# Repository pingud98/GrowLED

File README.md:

# GrowLED
PCB for red and blue LEDs

I had some spare Bivar SMP4-SBC-RB PLCC4 footprint LED's lying around so decided to make a board to use them in my hydroponics system.

All files are eagle cad. I've also panelised them to a 10x10cm board with 7 strips.

Licensed under the CERN OHL V1.2

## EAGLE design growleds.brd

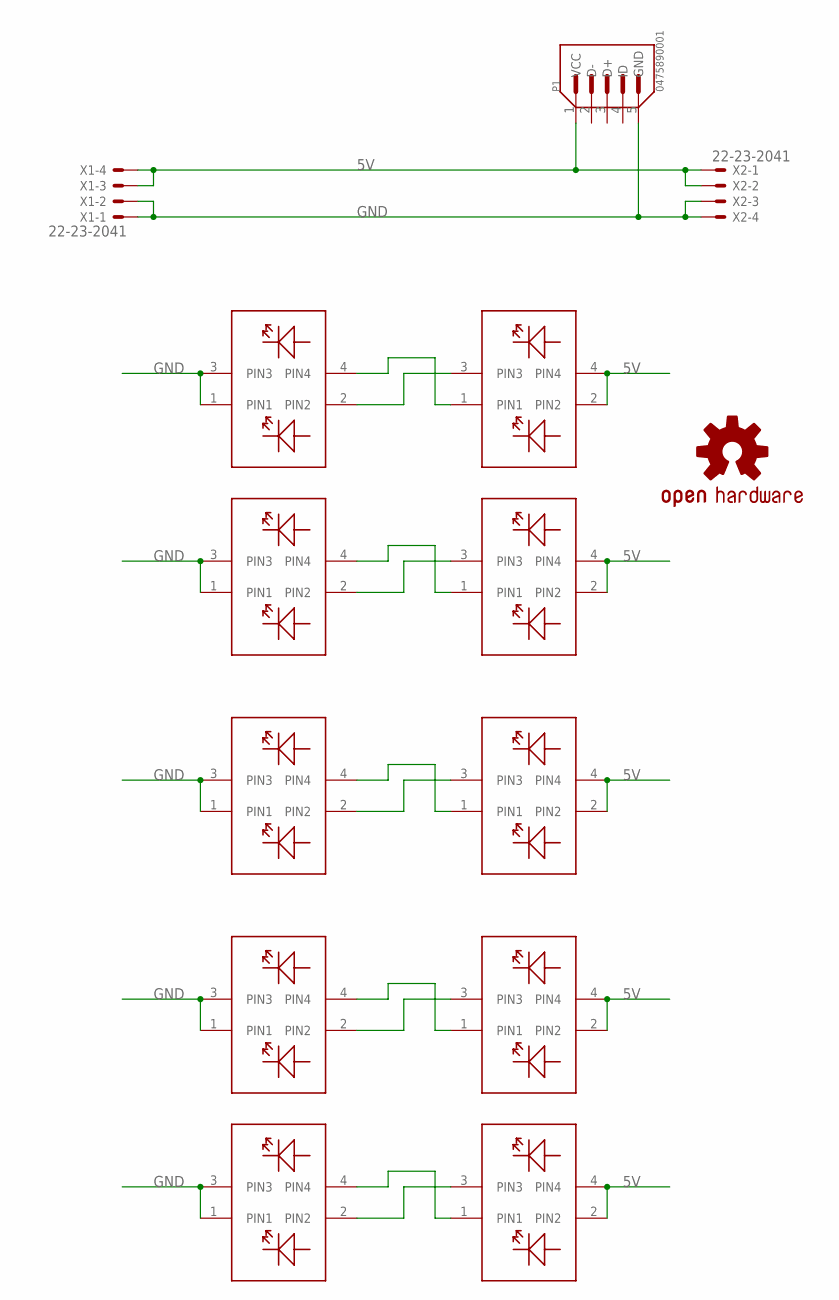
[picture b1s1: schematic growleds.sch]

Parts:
LOGO1: OSHW-LOGOM-COPPER; OSHW-LOGO-M_COPPER
P1: 0475890001; MOLEX_0475890001
U$1, U$2, U$3, U$4, U$5, U$6, U$7, U$8, U$9, U$10: RBLED; 4-PLCC
X1, X2: 22-23-2041

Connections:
5V: P1.1 (VCC), U$2.2 (PIN2), U$2.4 (PIN4), U$4.2 (PIN2), U$4.4 (PIN4), U$6.2 (PIN2), U$6.4 (PIN4), U$8.2 (PIN2), U$8.4 (PIN4), U$10.2 (PIN2), U$10.4 (PIN4), X1.3, X1.4, X2.1, X2.2
GND: P1.5 (GND), U$1.1 (PIN1), U$1.3 (PIN3), U$3.1 (PIN1), U$3.3 (PIN3), U$5.1 (PIN1), U$5.3 (PIN3), U$7.1 (PIN1), U$7.3 (PIN3), U$9.1 (PIN1), U$9.3 (PIN3), X1.1, X1.2, X2.3, X2.4
unnamed: U$1.2 (PIN2), U$2.3 (PIN3)
unnamed: U$1.4 (PIN4), U$2.1 (PIN1)
unnamed: U$3.2 (PIN2), U$4.3 (PIN3)
unnamed: U$3.4 (PIN4), U$4.1 (PIN1)
unnamed: U$5.2 (PIN2), U$6.3 (PIN3)
unnamed: U$5.4 (PIN4), U$6.1 (PIN1)
unnamed: U$7.2 (PIN2), U$8.3 (PIN3)
unnamed: U$7.4 (PIN4), U$8.1 (PIN1)
unnamed: U$9.2 (PIN2), U$10.3 (PIN3)
unnamed: U$9.4 (PIN4), U$10.1 (PIN1)

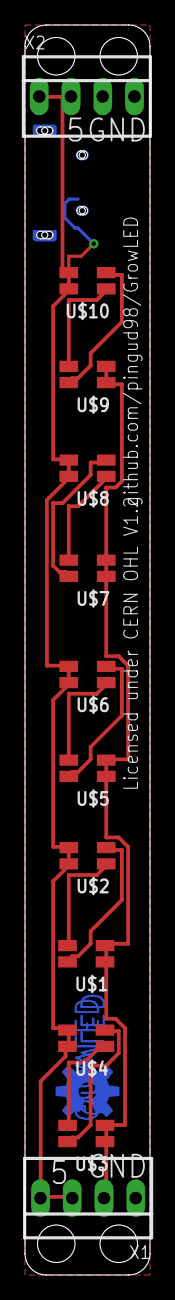
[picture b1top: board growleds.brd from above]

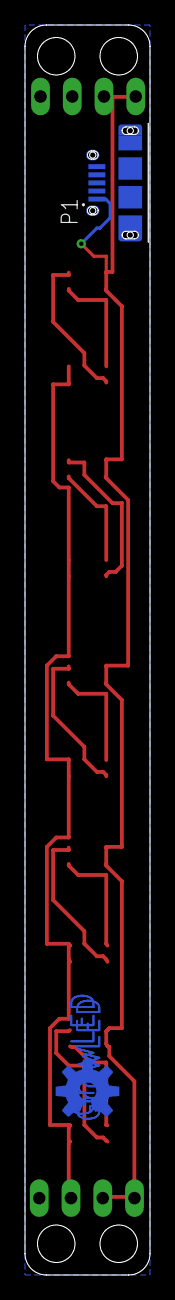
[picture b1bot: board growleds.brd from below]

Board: 2 copper layers, 10.0 x 100.0 mm, 14 parts (2 on the bottom side), 12 nets.

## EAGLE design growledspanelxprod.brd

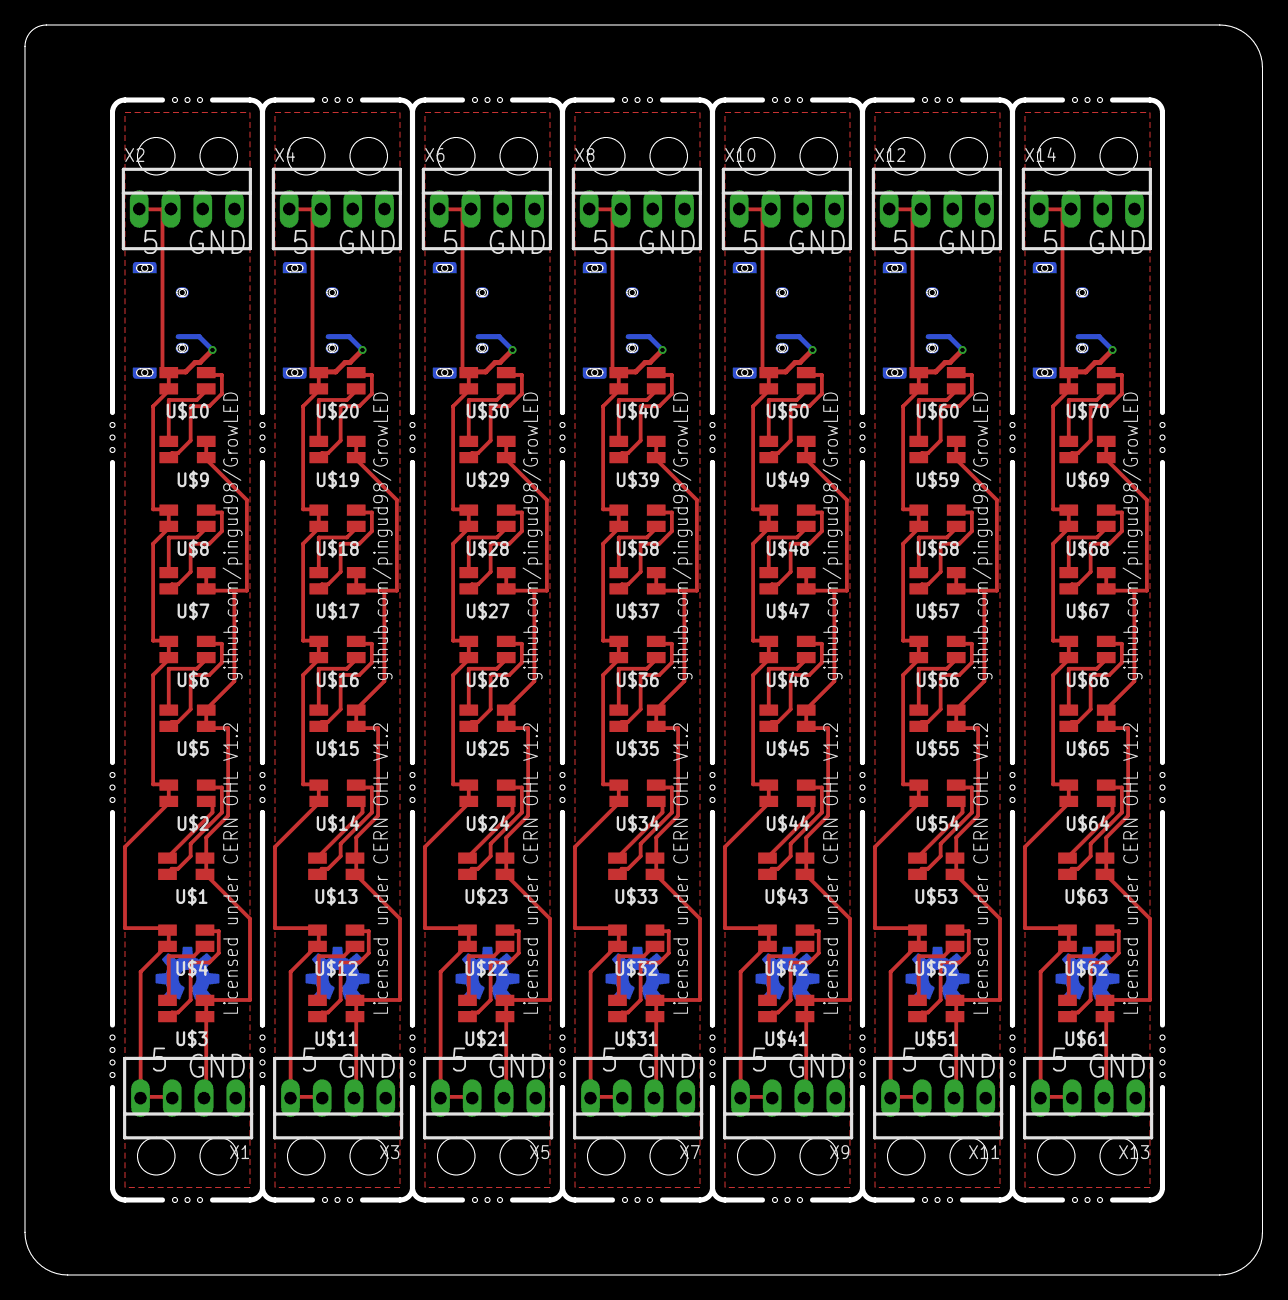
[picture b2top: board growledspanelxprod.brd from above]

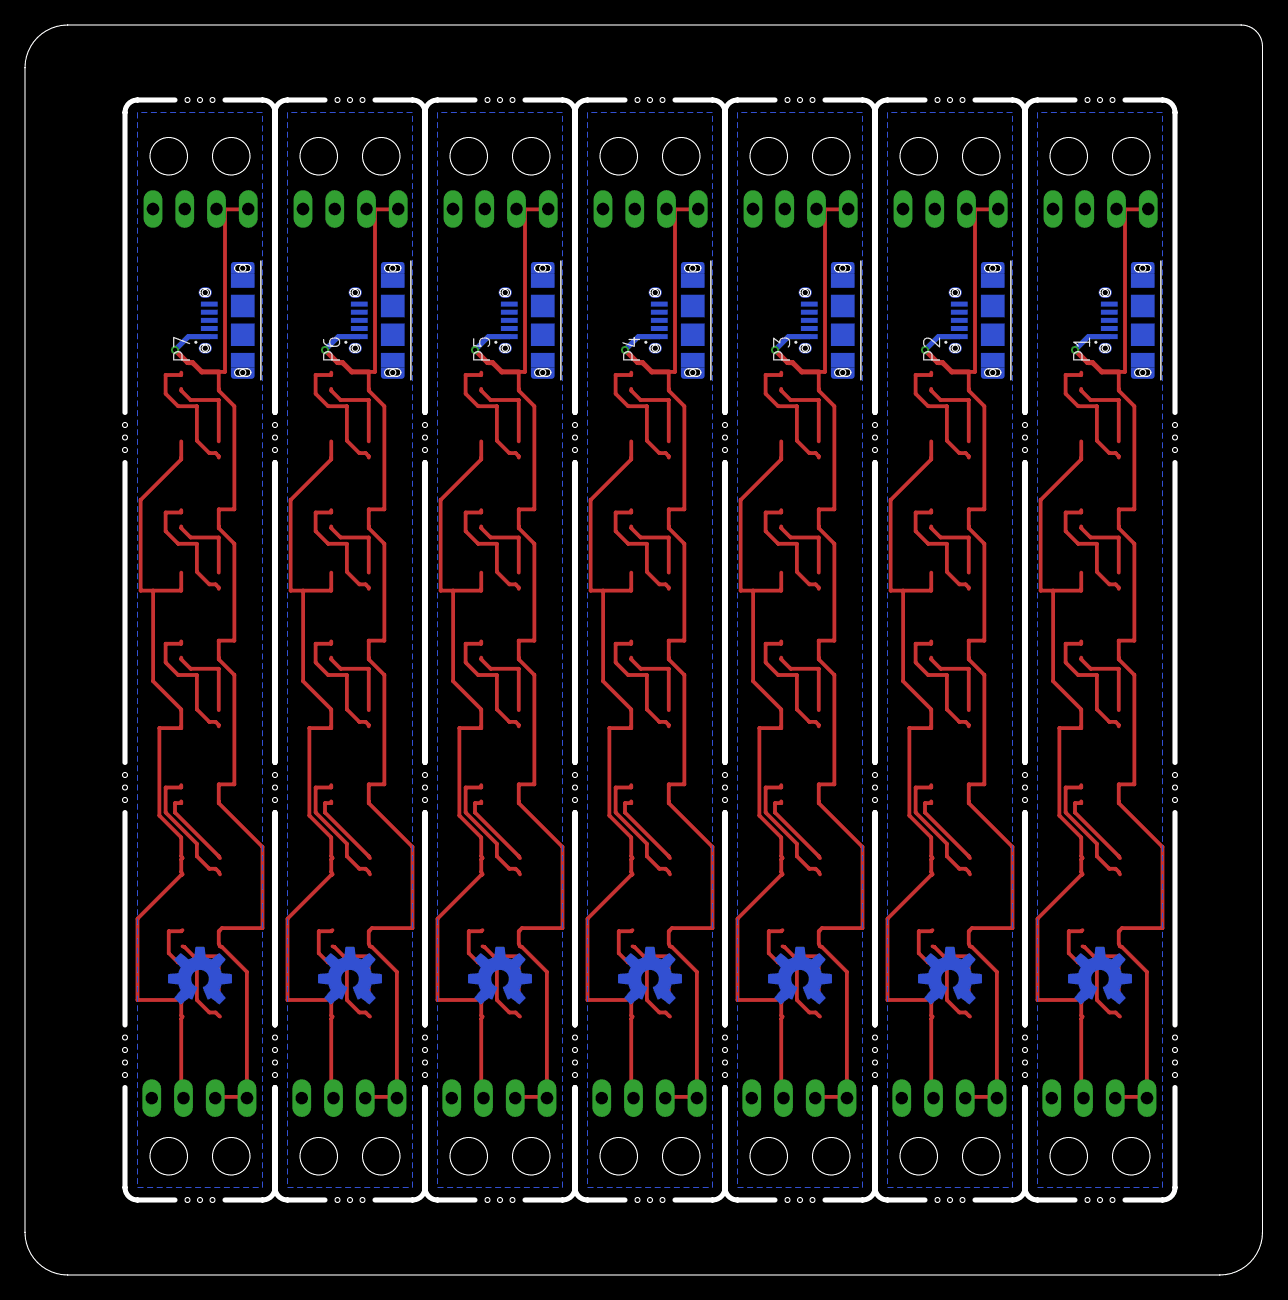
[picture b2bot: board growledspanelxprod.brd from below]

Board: 2 copper layers, 98.6 x 99.6 mm, 98 parts (14 on the bottom side), 84 nets.

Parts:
LOGO1, LOGO2, LOGO3, LOGO4, LOGO5, LOGO6, LOGO7: OSHW-LOGOM-COPPER; OSHW-LOGO-M_COPPER
P1, P2, P3, P4, P5, P6, P7: 0475890001; MOLEX_0475890001
U$1, U$2, U$3, U$4, U$5, U$6, U$7, U$8, U$9, U$10, U$11, U$12, U$13, U$14, U$15, U$16, U$17, U$18, U$19, U$20, U$21, U$22, U$23, U$24, U$25, U$26, U$27, U$28, U$29, U$30, U$31, U$32, U$33, U$34, U$35, U$36, U$37, U$38, U$39, U$40, U$41, U$42, U$43, U$44, U$45, U$46, U$47, U$48, U$49, U$50, U$51, U$52, U$53, U$54, U$55, U$56, U$57, U$58, U$59, U$60, U$61, U$62, U$63, U$64, U$65, U$66, U$67, U$68, U$69, U$70: RBLED; 4-PLCC
X1, X2, X3, X4, X5, X6, X7, X8, X9, X10, X11, X12, X13, X14: 22-23-2041

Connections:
5V: P1.1, U$2.2, U$2.4, U$4.2, U$4.4, U$6.2, U$6.4, U$8.2, U$8.4, U$10.2, U$10.4, X1.3, X1.4, X2.1, X2.2
5V1: P2.1, U$12.2, U$12.4, U$14.2, U$14.4, U$16.2, U$16.4, U$18.2, U$18.4, U$20.2, U$20.4, X3.3, X3.4, X4.1, X4.2
5V2: P3.1, U$22.2, U$22.4, U$24.2, U$24.4, U$26.2, U$26.4, U$28.2, U$28.4, U$30.2, U$30.4, X5.3, X5.4, X6.1, X6.2
5V3: P4.1, U$32.2, U$32.4, U$34.2, U$34.4, U$36.2, U$36.4, U$38.2, U$38.4, U$40.2, U$40.4, X7.3, X7.4, X8.1, X8.2
5V4: P5.1, U$42.2, U$42.4, U$44.2, U$44.4, U$46.2, U$46.4, U$48.2, U$48.4, U$50.2, U$50.4, X9.3, X9.4, X10.1, X10.2
5V5: P6.1, U$52.2, U$52.4, U$54.2, U$54.4, U$56.2, U$56.4, U$58.2, U$58.4, U$60.2, U$60.4, X11.3, X11.4, X12.1, X12.2
5V6: P7.1, U$62.2, U$62.4, U$64.2, U$64.4, U$66.2, U$66.4, U$68.2, U$68.4, U$70.2, U$70.4, X13.3, X13.4, X14.1, X14.2
GND: P1.5, U$1.1, U$1.3, U$3.1, U$3.3, U$5.1, U$5.3, U$7.1, U$7.3, U$9.1, U$9.3, X1.1, X1.2, X2.3, X2.4
GND1: P2.5, U$11.1, U$11.3, U$13.1, U$13.3, U$15.1, U$15.3, U$17.1, U$17.3, U$19.1, U$19.3, X3.1, X3.2, X4.3, X4.4
GND2: P3.5, U$21.1, U$21.3, U$23.1, U$23.3, U$25.1, U$25.3, U$27.1, U$27.3, U$29.1, U$29.3, X5.1, X5.2, X6.3, X6.4
GND3: P4.5, U$31.1, U$31.3, U$33.1, U$33.3, U$35.1, U$35.3, U$37.1, U$37.3, U$39.1, U$39.3, X7.1, X7.2, X8.3, X8.4
GND4: P5.5, U$41.1, U$41.3, U$43.1, U$43.3, U$45.1, U$45.3, U$47.1, U$47.3, U$49.1, U$49.3, X9.1, X9.2, X10.3, X10.4
GND5: P6.5, U$51.1, U$51.3, U$53.1, U$53.3, U$55.1, U$55.3, U$57.1, U$57.3, U$59.1, U$59.3, X11.1, X11.2, X12.3, X12.4
GND6: P7.5, U$61.1, U$61.3, U$63.1, U$63.3, U$65.1, U$65.3, U$67.1, U$67.3, U$69.1, U$69.3, X13.1, X13.2, X14.3, X14.4
unnamed: U$1.2, U$2.3
unnamed: U$1.4, U$2.1
unnamed: U$3.2, U$4.3
unnamed: U$3.4, U$4.1
unnamed: U$5.2, U$6.3
unnamed: U$5.4, U$6.1
unnamed: U$7.2, U$8.3
unnamed: U$7.4, U$8.1
unnamed: U$9.2, U$10.3
unnamed: U$9.4, U$10.1
unnamed: U$11.2, U$12.3
unnamed: U$11.4, U$12.1
unnamed: U$13.2, U$14.3
unnamed: U$13.4, U$14.1
unnamed: U$15.2, U$16.3
unnamed: U$15.4, U$16.1
unnamed: U$17.2, U$18.3
unnamed: U$17.4, U$18.1
unnamed: U$19.2, U$20.3
unnamed: U$19.4, U$20.1
unnamed: U$21.2, U$22.3
unnamed: U$21.4, U$22.1
unnamed: U$23.2, U$24.3
unnamed: U$23.4, U$24.1
unnamed: U$25.2, U$26.3
unnamed: U$25.4, U$26.1
unnamed: U$27.2, U$28.3
unnamed: U$27.4, U$28.1
unnamed: U$29.2, U$30.3
unnamed: U$29.4, U$30.1
unnamed: U$31.2, U$32.3
unnamed: U$31.4, U$32.1
unnamed: U$33.2, U$34.3
unnamed: U$33.4, U$34.1
unnamed: U$35.2, U$36.3
unnamed: U$35.4, U$36.1
unnamed: U$37.2, U$38.3
unnamed: U$37.4, U$38.1
unnamed: U$39.2, U$40.3
unnamed: U$39.4, U$40.1
unnamed: U$41.2, U$42.3
unnamed: U$41.4, U$42.1
unnamed: U$43.2, U$44.3
unnamed: U$43.4, U$44.1
unnamed: U$45.2, U$46.3
unnamed: U$45.4, U$46.1
unnamed: U$47.2, U$48.3
unnamed: U$47.4, U$48.1
unnamed: U$49.2, U$50.3
unnamed: U$49.4, U$50.1
unnamed: U$51.2, U$52.3
unnamed: U$51.4, U$52.1
unnamed: U$53.2, U$54.3
unnamed: U$53.4, U$54.1
unnamed: U$55.2, U$56.3
unnamed: U$55.4, U$56.1
unnamed: U$57.2, U$58.3
unnamed: U$57.4, U$58.1
unnamed: U$59.2, U$60.3
unnamed: U$59.4, U$60.1
unnamed: U$61.2, U$62.3
unnamed: U$61.4, U$62.1
unnamed: U$63.2, U$64.3
unnamed: U$63.4, U$64.1
unnamed: U$65.2, U$66.3
unnamed: U$65.4, U$66.1
unnamed: U$67.2, U$68.3
unnamed: U$67.4, U$68.1
unnamed: U$69.2, U$70.3
unnamed: U$69.4, U$70.1

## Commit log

2017-09-12 Added license documents

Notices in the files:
growleds.brd:
Licensed under CERN OHL V1.2
parts and their libraries:
SparkFun-Aesthetics: Licensing: Creative Commons ShareAlike 4.0 International - https://creativecommons.org/licenses/by-sa/4.0
